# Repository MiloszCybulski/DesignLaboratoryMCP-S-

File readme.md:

# Design Laboratory — MCP-S

Repozytorium projektu realizowanego w ramach przedmiotu **Design Laboratory (2025/26)**.  
Celem projektu jest zaprojektowanie i uruchomienie układu elektronicznego wraz z oprogramowaniem (m.in. obsługa wyświetlacza 7-segmentowego oraz rozszerzeń czujnikowych), a także zebranie dokumentacji technicznej.

Autorzy:
- Paweł Ścibek
- Sylwester Ślusarczyk
- Miłosz Cybulski

Dokumentację końcową projektu można znaleźć pod następującym linkiem: [Dokumentacja projektu](https://docs.google.com/document/d/1e8B4XN3sytEK4NsDrXsqLLuhZmmhayYSinMeYGpmRww/edit?tab=t.0)

## Instrukcje

Kod źródłowy do płytki AVR znajduje się w pliku `code/avr_final.c`.

Aby uruchomić aplikację, należy wykonać poniższą komendę trzeba z katalogu root projektu wykonać:

``` bash
cd code/
```
A nastepnie komendę: 

```bash
python3 AVR_Interface.py
```

## ENG Version

Repository for the project conducted as part of the **Design Laboratory (2025/26)** course.  
The goal of the project is to design and implement an electronic system along with software (including 7-segment display handling and sensor extensions), as well as to compile technical documentation.

Authors:
- Paweł Ścibek
- Sylwester Ślusarczyk
- Miłosz Cybulski

The final project documentation can be found at the following link: [Project Documentation](https://docs.google.com/document/d/1e8B4XN3sytEK4NsDrXsqLLuhZmmhayYSinMeYGpmRww/edit?tab=t.0)

## Instructions

The source code for the AVR board can be found in the file `code/avr_final.c`.

To run the application, execute the following command from the root directory of the project:

``` bash
cd code/
```
Then, run the command:
``` bash
python3 AVR_Interface.py
```

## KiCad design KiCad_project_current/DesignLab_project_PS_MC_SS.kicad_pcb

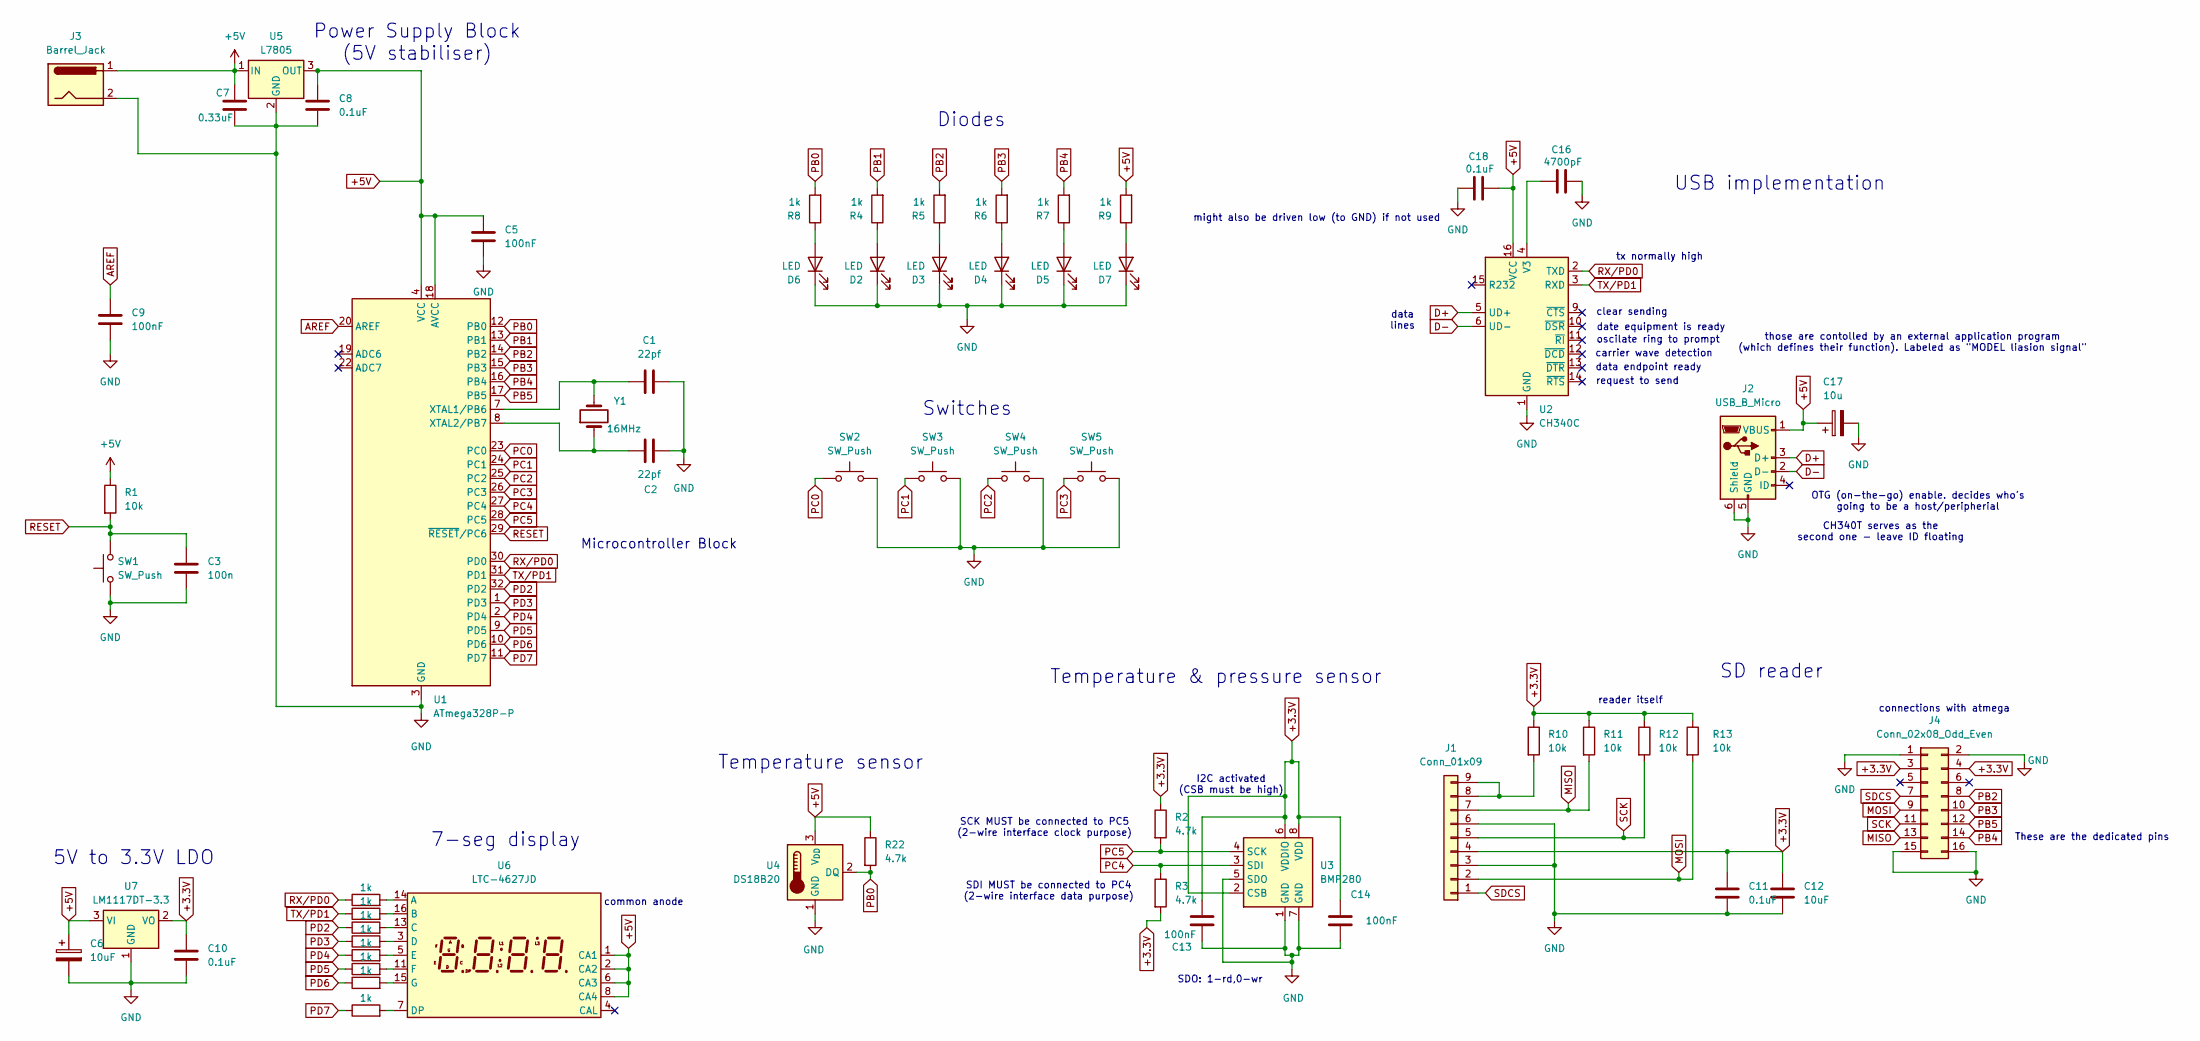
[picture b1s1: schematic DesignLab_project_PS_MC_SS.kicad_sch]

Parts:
C1, C2: 22pf; C_0603_1608Metric
C3: 100n; C_0603_1608Metric
C5, C9, C13, C14: 100nF; C_0603_1608Metric
C6: 10uF; CP_Elec_4x3
C7: 0.33uF; C_0603_1608Metric
C8, C10, C11, C18: 0.1uF; C_0603_1608Metric
C12: 10uF; C_0603_1608Metric
C16: 4700pF; C_0603_1608Metric
C17: 10u; CP_Elec_4x3
D2, D3, D4, D5, D6, D7: LED; LED_0603_1608Metric
J1: Conn_01x09; PinHeader_1x09_P2.54mm_Vertical
J2: USB_B_Micro; USB_Micro-B_Molex-105017-0001
J3: Barrel_Jack; BarrelJack_Horizontal
J4: Conn_02x08_Odd_Even; PinHeader_2x08_P2.54mm_Vertical
R1, R10, R11, R12, R13: 10k; R_0805_2012Metric_Pad1.20x1.40mm_HandSolder
R2, R3, R22: 4.7k; R_0805_2012Metric_Pad1.20x1.40mm_HandSolder
R4, R5, R6, R7, R8, R9, R14, R15, R16, R17, R18, R19, R20, R21: 1k; R_0805_2012Metric_Pad1.20x1.40mm_HandSolder
SW1, SW2, SW3, SW4, SW5: SW_Push; SW_Tactile_SPST_NO_Straight_CK_PTS636Sx25SMTRLFS
U1: ATmega328P-P; TQFP-32_7x7mm_P0.8mm
U2: CH340C; SOIC-16_3.9x9.9mm_P1.27mm
U3: BMP280; Bosch_LGA-8_2x2.5mm_P0.65mm_ClockwisePinNumbering
U4: DS18B20; TO-92_Inline
U5: L7805; TO-252-2
U6: LTC-4627JD; LTC-4627Jx
U7: LM1117DT-3.3; TO-252-3_TabPin2
Y1: 16MHz; Oscillator_SMD_Abracon_ASDMB-4Pin_2.5x2.0mm

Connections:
+3.3V: C10.1, C11.1, C12.1, C13.2, C14.1, J1.4, J4.3, J4.4, R2.1, R3.2, R10.1, R11.1, R12.1, R13.1, U3.2 (CSB), U3.6 (VDDIO), U3.8 (VDD), U7.2 (VO)
+5V: C5.1, C6.1, C7.1, C8.1, C17.1, C18.2, J2.1 (VBUS), J3.1, R1.1, R9.2, R22.1, U1.4 (VCC), U1.6 (VCC), U1.18 (AVCC), U2.16 (VCC), U4.3 (V_{DD}), U5.1 (IN), U5.3 (OUT), U6.1 (CA1), U6.2 (CA2), U6.6 (CA3), U6.8 (CA4), U7.3 (VI)
AREF: C9.1, U1.20 (AREF)
D+: J2.3 (D+), U2.5 (UD+)
D-: J2.2 (D-), U2.6 (UD-)
GND: C1.2, C2.2, C3.2, C5.2, C6.2, C7.2, C8.2, C9.2, C10.2, C11.2, C12.2, C13.1, C14.2, C16.2, C17.2, C18.1, D2.1 (K), D3.1 (K), D4.1 (K), D5.1 (K), D6.1 (K), D7.1 (K), J1.3, J1.6, J2.5 (GND), J2.6 (Shield), J3.2, J4.1, J4.2, J4.15, J4.16, SW1.1, SW2.2, SW3.2, SW4.2, SW5.2, U1.3 (GND), U1.5 (GND), U1.21 (GND), U2.1 (GND), U3.1 (GND), U3.5 (SDO), U3.7 (GND), U4.1 (GND), U5.2 (GND), U7.1 (GND)
MISO: J1.7, J4.13, R11.2
MOSI: J1.2, J4.9, R13.2
unnamed: D2.2 (A), R4.1
unnamed: D3.2 (A), R5.1
unnamed: D4.2 (A), R6.1
unnamed: D5.2 (A), R7.1
unnamed: D6.2 (A), R8.1
unnamed: D7.2 (A), R9.1
unnamed: J1.8, J1.9, R10.2
unnamed: C1.1, U1.7 (XTAL1/PB6), Y1.2
unnamed: C2.1, U1.8 (XTAL2/PB7), Y1.1
unnamed: C16.1, U2.4 (V3)
unnamed: R14.2, U6.14 (A)
unnamed: R15.2, U6.16 (B)
unnamed: R16.2, U6.13 (C)
unnamed: R17.2, U6.3 (D)
unnamed: R21.2, U6.7 (DP)
unnamed: R18.2, U6.5 (E)
unnamed: R19.2, U6.11 (F)
unnamed: R20.2, U6.15 (G)
PB0: R8.2, R22.2, U1.12 (PB0), U4.2 (DQ)
PB1: R4.2, U1.13 (PB1)
PB2: J4.8, R5.2, U1.14 (PB2)
PB3: J4.10, R6.2, U1.15 (PB3)
PB4: J4.14, R7.2, U1.16 (PB4)
PB5: J4.12, U1.17 (PB5)
PC0: SW2.1, U1.23 (PC0)
PC1: SW3.1, U1.24 (PC1)
PC2: SW4.1, U1.25 (PC2)
PC3: SW5.1, U1.26 (PC3)
PC4: R3.1, U1.27 (PC4), U3.3 (SDI)
PC5: R2.2, U1.28 (PC5), U3.4 (SCK)
PD2: R16.1, U1.32 (PD2)
PD3: R17.1, U1.1 (PD3)
PD4: R18.1, U1.2 (PD4)
PD5: R19.1, U1.9 (PD5)
PD6: R20.1, U1.10 (PD6)
PD7: R21.1, U1.11 (PD7)
RESET: C3.1, R1.2, SW1.2, U1.29 (~RESET/PC6)
RX/PD0: R14.1, U1.30 (PD0), U2.2 (TXD)
SCK: J1.5, J4.11, R12.2
SDCS: J1.1, J4.7
TX/PD1: R15.1, U1.31 (PD1), U2.3 (RXD)

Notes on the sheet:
USB implementation
data endpoint ready
Diodes
clear sending
SDI MUST be connected to PC4 (2-wire interface data purpose)
Power Supply Block (5V stabiliser)
Switches
connections with atmega
SD reader
data lines
tx normally high
common anode
5V to 3.3V LDO
7-seg display
Temperature & pressure sensor
oscilate ring to prompt
request to send
Temperature sensor
might also be driven low (to GND) if not used
Microcontroller Block
These are the dedicated pins
SCK MUST be connected to PC5 (2-wire interface clock purpose)
SDO: 1-rd,0-wr
OTG (on-the-go) enable. decides who's going to be a host/peripherial
reader itself
those are contolled by an external application program (which defines their function). Labeled as "MODEL liasion signal"
CH340T serves as the second one - leave ID floating
date equipment is ready
carrier wave detection
I2C activated (CSB must be high)

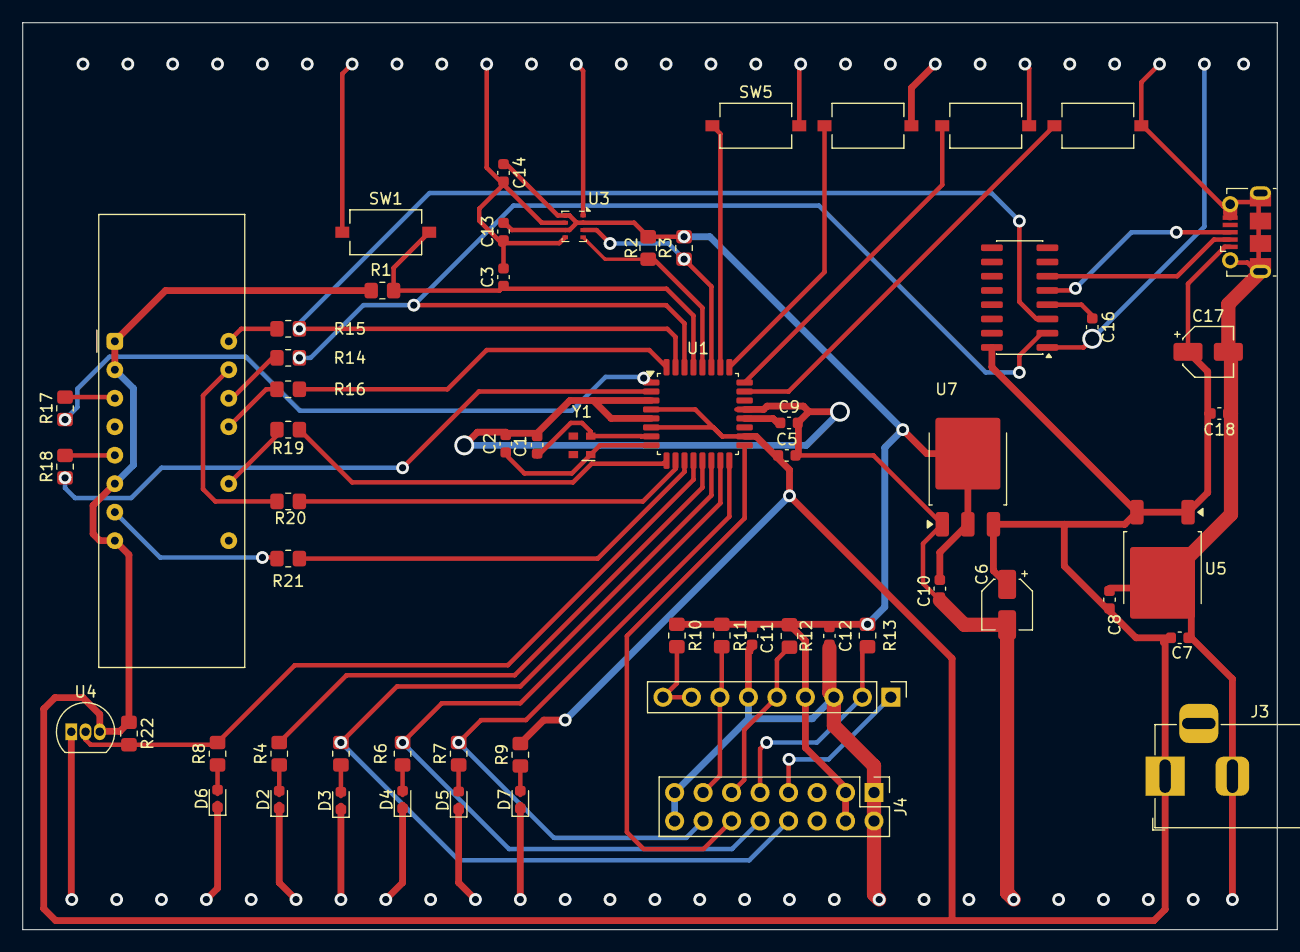
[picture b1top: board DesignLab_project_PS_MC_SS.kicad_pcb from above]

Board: 2 copper layers, 111.9 x 80.9 mm, 61 parts (0 on the bottom side), 49 nets.

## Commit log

2025-10-27 Create koddopłytki_V1.0
    Kod do płytki zawierający sterowanie LED oraz płytką przyciskową
2025-10-27 kod do płytki V_1.5
    //próbny kod płytki LED + płytka przyciskowa + wyświetlacz 7 seg + karta sd, aktualnie kod wyświetla liczby od 0 do 9 sprawdzając działanie i połączenia wyświetlaczu 7 seg, kod do czytnika karty sd j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
2025-11-06 Revise readme with project details for Design Laboratory
    Updated project description and objectives.
2025-11-06 Update README with project description
2025-11-06 Add authors section to the README
2025-11-19 Create próbauarta
    próba kodowania uarta
2025-11-23 new project version 1.1
2025-11-30 Current version of the KiCad project
2025-12-07 Current version of KiCad project
2025-12-08 SYLWEK_VERSION_08.12.2025_15:15
    Fixed routes
2025-12-20 Final version of the KiCad project
2026-01-02 Update koddopłytki_Vfinal
2026-01-02 Update próbauarta+bmp28-
2026-01-02 Rename koddopłytki_V1.0 to koddopłytki_Vfinal
2026-01-02 Rename próbauarta to próbauarta+BMP komuikacja w obie strony
2026-01-03 ZIP of all important datasheets
2026-01-03 All datasheets used in the making of the project
2026-01-03 Update on a link to the final project documentation
2026-01-17 bug fix in C code and added interface to display data
2026-01-17 new filenames
2026-01-17 New structure
2026-01-17 Create DL_Project_Documentation
2026-01-17 Update README with project description
    Added English version of project documentation and instructions.
2026-01-17 Update and rename DL_Project_Documentation to n
